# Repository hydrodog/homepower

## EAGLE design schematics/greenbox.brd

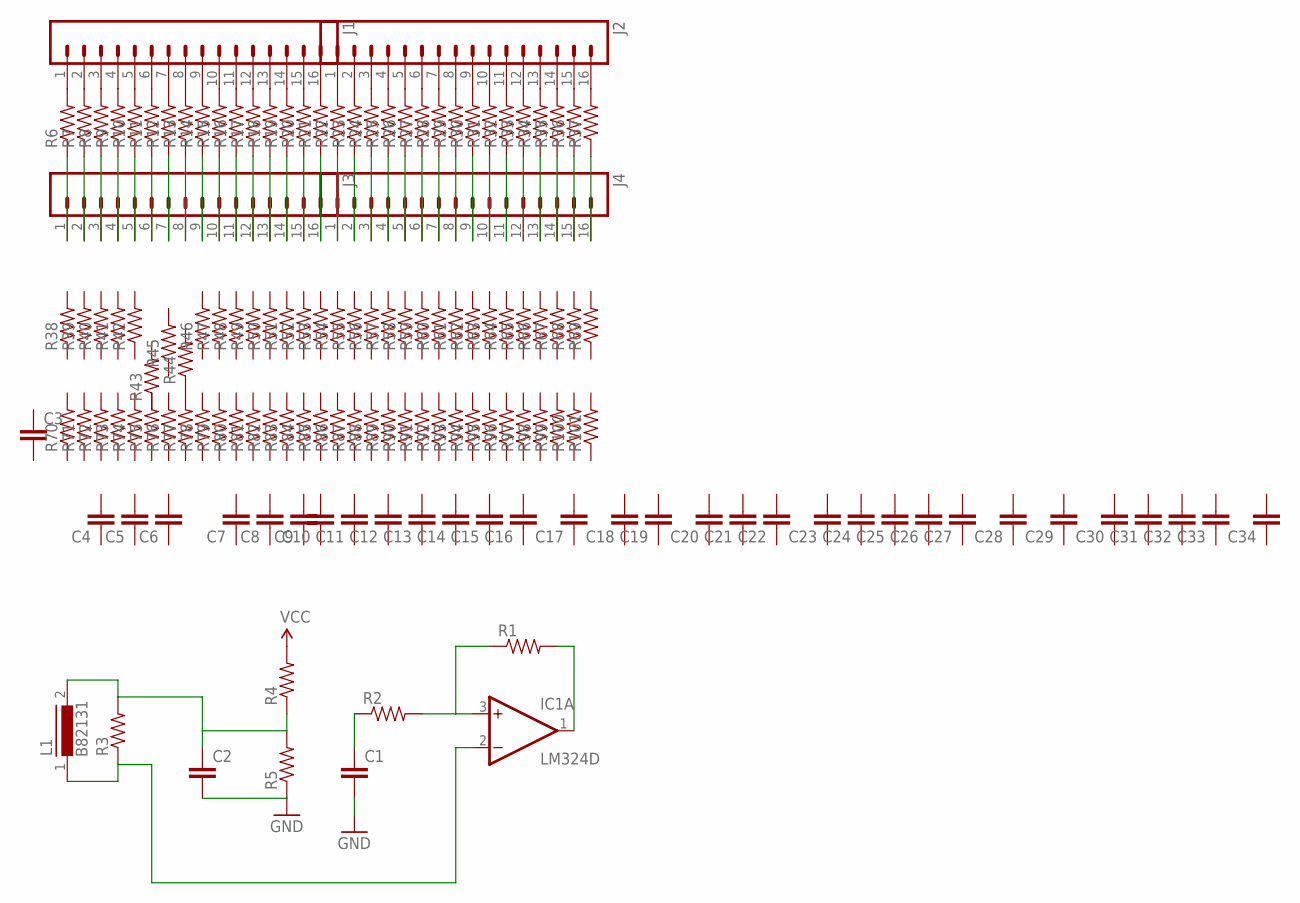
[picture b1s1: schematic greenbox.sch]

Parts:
C1, C2, C3, C4, C5, C6, C7, C8, C9, C10, C11, C12, C13, C14, C15, C16, C17, C18, C19, C20, C21, C22, C23, C24, C25, C26, C27, C28, C29, C30, C31, C32, C33, C34: CAP0603-CAP; 0603-CAP
IC1: LM324D; SO14
J1, J2, J3, J4: M16LOCK; 1X16_LOCK
L1: B82131; SUKW1-17
R1, R2: RESISTOR0603; 0603-RES
R3, R4, R5, R6, R7, R8, R9, R10, R11, R12, R13, R14, R15, R16, R17, R18, R19, R20, R21, R22, R23, R24, R25, R26, R27, R28, R29, R30, R31, R32, R33, R34, R35, R36, R37, R38, R39, R40, R41, R42, R43, R44, R45, R46, R47, R48, R49, R50, R51, R52, R53, R54, R55, R56, R57, R58, R59, R60, R61, R62, R63, R64, R65, R66, R67, R68, R69, R70, R71, R72, R73, R74, R75, R76, R77, R78, R79, R80, R81, R82, R83, R84, R85, R86, R87, R88, R89, R90, R91, R92, R93, R94, R95, R96, R97, R98, R99, R100, R101: RESISTOR0603-RES; 0603-RES

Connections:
GND: C1.2, C2.2, R5.1
unnamed: IC1.1 (OUT), R1.2
unnamed: C2.1, L1.2, R3.2, R4.1, R5.2
unnamed: C1.1, R2.1
unnamed: IC1.2 (-IN), L1.1, R3.1
unnamed: R44.1, R77.2
unnamed: J3.1, R6.1
unnamed: J3.2, R7.1
unnamed: J3.3, R8.1
unnamed: J3.4, R9.1
unnamed: J3.5, R10.1
unnamed: J3.6, R11.1
unnamed: J3.7, R12.1
unnamed: J3.8, R13.1
unnamed: J3.9, R14.1
unnamed: J3.10, R15.1
unnamed: J3.11, R16.1
unnamed: J3.12, R17.1
unnamed: J3.13, R18.1
unnamed: J3.14, R19.1
unnamed: J3.15, R20.1
unnamed: J3.16, R21.1
unnamed: J4.1, R22.1
unnamed: J4.2, R23.1
unnamed: J4.3, R24.1
unnamed: J4.4, R25.1
unnamed: J4.5, R26.1
unnamed: J4.6, R27.1
unnamed: J4.7, R28.1
unnamed: J4.8, R29.1
unnamed: J4.9, R30.1
unnamed: J4.10, R31.1
unnamed: J4.11, R32.1
unnamed: J4.12, R33.1
unnamed: J4.13, R34.1
unnamed: J4.14, R35.1
unnamed: J4.15, R36.1
unnamed: J4.16, R37.1
unnamed: J1.1, R6.2
unnamed: J1.2, R7.2
unnamed: J1.3, R8.2
unnamed: J1.4, R9.2
unnamed: J1.5, R10.2
unnamed: J1.6, R11.2
unnamed: J1.7, R12.2
unnamed: J1.8, R13.2
unnamed: J1.9, R14.2
unnamed: J1.10, R15.2
unnamed: J1.11, R16.2
unnamed: J1.12, R17.2
unnamed: J1.13, R18.2
unnamed: J1.14, R19.2
unnamed: J1.15, R20.2
unnamed: J1.16, R21.2
unnamed: J2.1, R22.2
unnamed: J2.2, R23.2
unnamed: J2.3, R24.2
unnamed: J2.4, R25.2
unnamed: J2.5, R26.2
unnamed: J2.6, R27.2
unnamed: J2.7, R28.2
unnamed: J2.8, R29.2
unnamed: J2.9, R30.2
unnamed: J2.10, R31.2
unnamed: J2.11, R32.2
unnamed: J2.12, R33.2
unnamed: J2.13, R34.2
unnamed: J2.14, R35.2
unnamed: J2.15, R36.2
unnamed: J2.16, R37.2
V+: IC1.4 (V+)
V-: IC1.11 (V-)
VCC: R4.2
VIN: IC1.3 (+IN), R1.1, R2.2

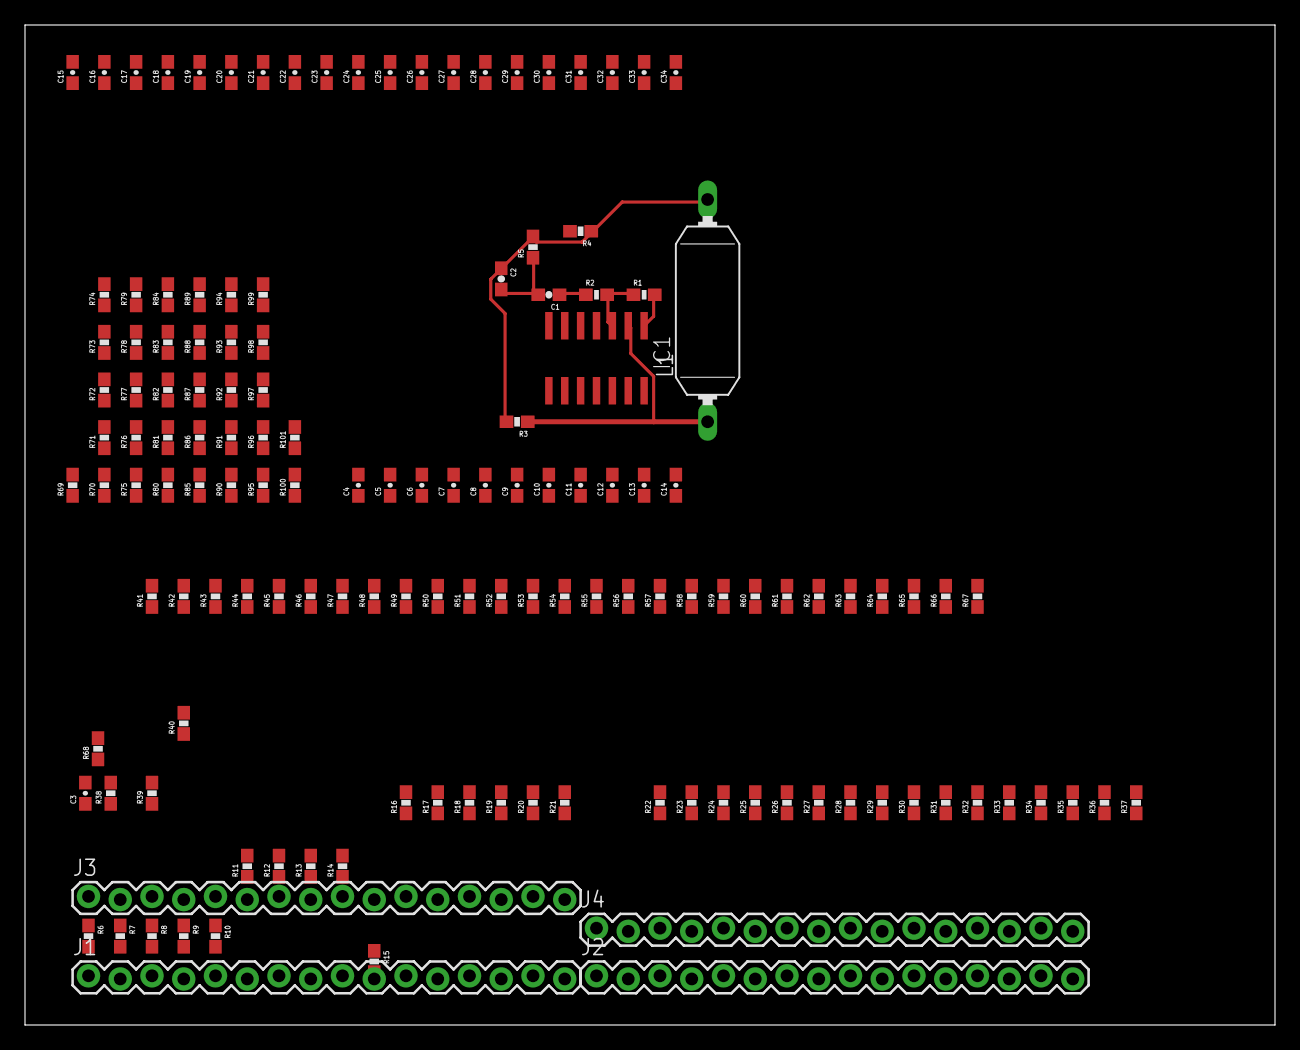
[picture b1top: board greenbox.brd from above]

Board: 2 copper layers, 100.0 x 80.0 mm, 141 parts (0 on the bottom side), 71 nets.

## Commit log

2016-09-19 initial commit, rough schematics to get started

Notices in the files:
parts and their libraries:
SparkFun-Passives: Licensing: Creative Commons ShareAlike 4.0 International - https://creativecommons.org/licenses/by-sa/4.0
